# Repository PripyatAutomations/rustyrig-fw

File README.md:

# RustyRig

**Share radios, audio, and station resources over a network.**

RustyRig is a GPLv2-licensed, open-source, multi-user amateur-radio platform. Operate radios from another computer, listen with friends, or bring multiple stations together. Operators get live radio controls, audio, chat, and access to the resources they are allowed to use.

RustyRig is under active development. The current releases are for testing; features and configuration can change.

WebUI will be returning in v2.0! The v1.x series is focusing on improving
transport reliability by adding RTP (done!), mesh server links (almost done), 
and multihome client connections (pending).

Currently this is NOT usable out of the box on non-linux hosts, we'll revisit that soon with libmongoose!

## What you can do

- **Operate together.** Join radio rooms, see who's online, chat, and coordinate transmitter access.
- **Control more than one radio.** Work with supported Hamlib radios and networked rig-control backends.
- **Listen and transmit remotely.** Route receive and transmit audio over the network, with codec selection and per-stream controls.
- **Choose your interface.** Use the Linux GTK desktop client, terminal client, or browser interface.
- **Connect stations.** Link servers to access authorized remote rooms and station resources.
- **Explore SDR receivers.** Browse and connect to supported remote receivers through the SDR Directory.

Additional tools include remote serial/GPS access, audio recording, administration, and station resource discovery.

## See it in action

| Desktop client | Terminal client |
| --- | --- |
|  |  |

| Settings | Browser client |
| --- | --- |
|  |  |

| SDR Browser | SDR Receiver |
| --- | --- |
|  |  |

### Resource Explorer

### Audio Routing

## Get started

RustyRig currently targets Debian-family Linux distributions for building and packaging.

The recommended multi-project build is [rrpk](https://github.com/PripyatAutomations/rrpk),
which clones, builds and installs `librustyaxe`, `librrprotocol`,
`callsign-lookup`, and finally `rustyrig-fw` as independent repositories
in dependency order. **These three projects are not bundled or submodules of
rustyrig-fw.** For a standalone RustyRig build, install their respective
development packages first.

```sh
git clone https://github.com/PripyatAutomations/rustyrig-fw.git
# Install librustyaxe-dev, librrprotocol-dev and librustyirc-dev separately before building.
cd rustyrig-fw
./install-deps.sh
```

The native OpenSSL/wslay build does not fetch Mongoose or generate an EEPROM image.
Run `make PROFILE=radio buildconf` to generate only the application
configuration header; the normal `make PROFILE=radio` does that automatically.
Embedded EEPROM builds can opt in with `make PROFILE=radio USE_EEPROM=true`.
Mongoose is disabled by default and only fetched with an explicit
`USE_MONGOOSE=true` build/update through `tools/update-optional-sources.sh`.

The dependency helper prints the installation command for your selected build profile. Follow the instructions it produces, then continue with the **[quickstart](QUICKSTART.txt)** to build, configure a station, and connect your first client.

**New to RustyRig?** Start with a single server and one radio—or Hamlib's dummy backend—before enabling additional stations or transmit functions.

## Documentation

| Guide | When to read it |
| --- | --- |
| [Quickstart](QUICKSTART.txt) | First installation, login, and connection |
| [Operator guide](doc/operator-guide.md) | Tuning, audio, rooms, SDRs and troubleshooting |
| [Installation and packaging](doc/INSTALLING) | Package and service installation |
| [Radio rooms](doc/rig-rooms.md) | Multiple rigs, room access, and VFO/audio behavior |
| [Audio codecs](doc/media-codecs.md) | Selecting codecs and setting up audio pipelines |
| [IRC client settings](doc/irc-client.md) | Multiple connections and proxies |
| [Serial devices, server exports and privileges](doc/serial-interfaces.md) | Map physical UART/USB devices, grant per-device access, attach from clients, and understand mesh limitations |
| [Known issues](doc/KNOWN-ISSUES.md) | Open RC problems and requested fixes |
| [Changelog](CHANGELOG) | Recent changes and known transitions |
| [RC release checklist](doc/release-checklist.md) | Build, package, smoke-test and tag a release |
| [Release packaging guide](doc/RELEASING.md) | Debian RC versions, reproducible builds and upgrades |
| [Debian archive readiness](doc/debian-archive-readiness.md) | Sponsor-facing blockers, license inventory and clean-build checks |
| [Debian source/package split](doc/debian-source-split.md) | External library source packages and retained rrserver/rrclient/rrbridge binary split |
| [Server maintenance](doc/server-maintenance.md) | Confirmed database, log, recording and identity resets |
| [Remote SDR architecture](doc/remote-sdr-architecture.md) | Design proposal, **not implemented functionality** |

Configuration examples live in [`config/`](config/). Use `/help` in the client for commands.

## NOTES

This is an early version, especially backend.yaesu -- please don't use it
unattended until you test it thoroughly in your setup.

CAT emulator currently has very limited 991a support and you probably should
select ft891 in your program for now if trying to use it.

Yaesu backend has experimental support for ft991(a) support. If it doesnt
work well, let me know and in the meanwhile try hamlib backend.

## For developers

The main pieces are `rrserver` (server), `rrclient` (GTK/TUI), `rrbridge` (SDR bridges), `librrprotocol` (shared protocol), `librustyaxe` (application support), and `fwdsp` / `libfwdspmgr` (audio). The browser UI is developed in [rustyrig-www](https://github.com/PripyatAutomations/rustyrig-www).

Contributions, hardware compatibility reports, documentation improvements, and reproducible bug reports are welcome. See the [issue tracker](https://github.com/PripyatAutomations/rustyrig-fw/issues).

## License

RustyRig-owned code is licensed under the **GNU General Public License,
version 2 only** (`GPL-2.0-only`); see [doc/LICENSE](doc/LICENSE).
The independently installed `librrprotocol` library is GPLv2. The `librustyaxe` library retains
its MIT license. Other bundled components, dependencies and Windows themes
retain their respective upstream licenses.

For a complete mesh bootstrap or post-compromise credential rotation, see the
[cluster rebuild and breach-recovery runbook](doc/cluster-rebuild-recovery.md).

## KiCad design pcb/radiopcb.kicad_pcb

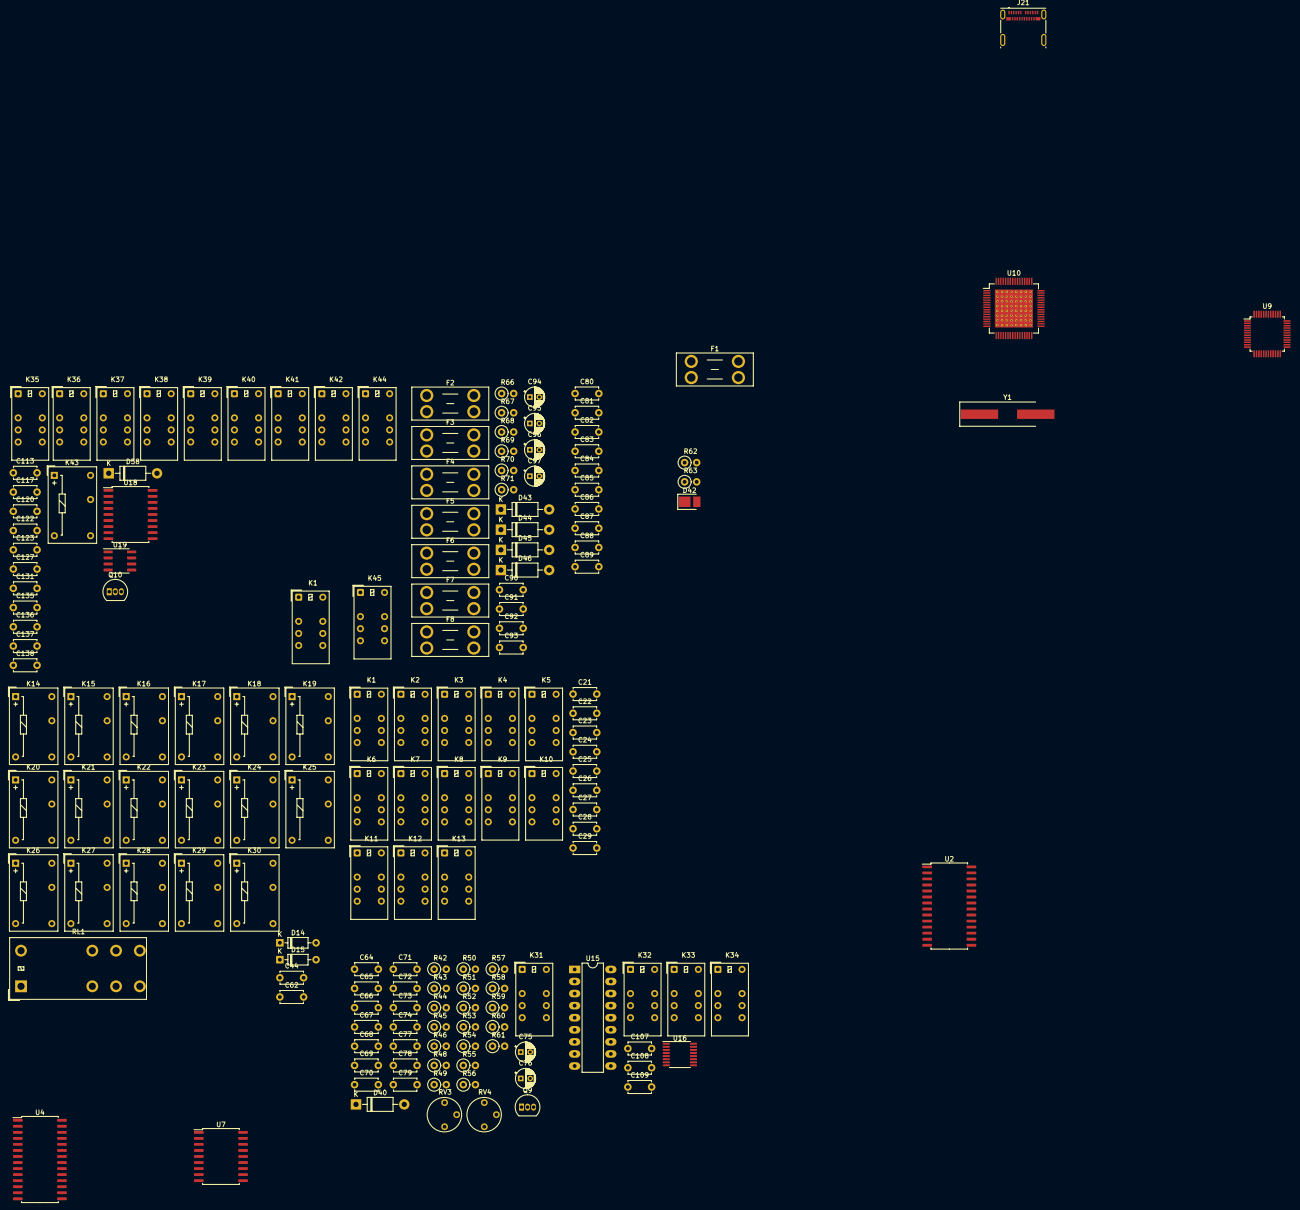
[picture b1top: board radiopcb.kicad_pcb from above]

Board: 2 copper layers, 165 parts (0 on the bottom side), 130 nets, no tracks yet.

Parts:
C21, C22, C23, C24, C25, C26, C27, C28, C29, C44, C62, C64, C65, C66, C67, C68, C69, C70, C71, C72, C73, C74, C77, C78, C79, C80, C81, C86, C87, C88, C89, C107, C108, C109, C113, C117, C120, C122, C123, C127, C131, C135, C136, C137, C138: 0.1u; C_Disc_D4.7mm_W2.5mm_P5.00mm
C75, C76: 470u; CP_Radial_D4.0mm_P2.00mm
C82, C83, C90: 10u; C_Disc_D4.7mm_W2.5mm_P5.00mm
C84, C85: 18p; C_Disc_D4.7mm_W2.5mm_P5.00mm
C91, C92: 100n; C_Disc_D4.7mm_W2.5mm_P5.00mm
C93: 47u; C_Disc_D4.7mm_W2.5mm_P5.00mm
C94, C95: 220u; CP_Radial_D4.0mm_P2.00mm
C96, C97: 10u; CP_Radial_D4.0mm_P2.00mm
D14, D15: 1N4148; D_DO-35_SOD27_P7.62mm_Horizontal
D40, D43, D44, D45, D46, D58: 1N4001; D_DO-41_SOD81_P10.16mm_Horizontal
D42: LED-Green; LED_PLCC_2835_Handsoldering
F1, F6: 3A; Fuseholder_Blade_Mini_Keystone_3568
F2, F3: 30A; Fuseholder_Blade_Mini_Keystone_3568
F4, F5: 5A; Fuseholder_Blade_Mini_Keystone_3568
F7, F8: 250mA; Fuseholder_Blade_Mini_Keystone_3568
J21: USB; USB_C_Receptacle_Molex_105450-0101
K1, K1#2, K2, K3, K4, K5, K6, K7, K8, K9, K10, K11, K12, K13, K31, K32, K33, K34, K35, K36, K37, K38, K39, K40, K41, K42, K44, K45: EC2-5SNU; Relay_DPDT_Kemet_EC2
K14, K15, K16, K17, K18, K19, K20, K21, K22, K23, K24, K25, K26, K27, K28, K29, K30, K43: G6E; Relay_SPDT_Omron_G6E
Q9: 2N3904; TO-92_Inline
Q10: BT169B; TO-92_Inline
R42, R43, R52, R53: 1K; R_Axial_DIN0207_L6.3mm_D2.5mm_P2.54mm_Vertical
R44, R45, R48, R49, R50, R51, R54, R55: 22; R_Axial_DIN0207_L6.3mm_D2.5mm_P2.54mm_Vertical
R46, R56: 2.2K; R_Axial_DIN0207_L6.3mm_D2.5mm_P2.54mm_Vertical
R57, R58: 47; R_Axial_DIN0207_L6.3mm_D2.5mm_P2.54mm_Vertical
R59, R60: 220; R_Axial_DIN0207_L6.3mm_D2.5mm_P2.54mm_Vertical
R61: 1k; R_Axial_DIN0207_L6.3mm_D2.5mm_P2.54mm_Vertical
R62, R68, R69, R70, R71: 10M; R_Axial_DIN0207_L6.3mm_D2.5mm_P2.54mm_Vertical
R63: 9.53K; R_Axial_DIN0207_L6.3mm_D2.5mm_P2.54mm_Vertical
R66: 10k; R_Axial_DIN0207_L6.3mm_D2.5mm_P2.54mm_Vertical
R67: 54.9k; R_Axial_DIN0207_L6.3mm_D2.5mm_P2.54mm_Vertical
RL1: Bypass; Relay_DPDT_Panasonic_JW2
RV3, RV4: 10K; Potentiometer_Vishay_T7-YA_Single_Vertical
U2, U4: MCP23017_SO; SOIC-28W_7.5x17.9mm_P1.27mm
U7, U18: MCP23008-xSO; SOIC-18W_7.5x11.6mm_P1.27mm
U9: CM119B; TQFP-48_7x7mm_P0.5mm
U10: TUSB4041I; HTQFP-64-1EP_10x10mm_P0.5mm_EP8x8mm_Mask4.4x4.4mm_ThermalVi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
U15: ULN2804A; DIP-18_W7.62mm_LongPads
U16: 74HC596; TSSOP-16_4.4x5mm_P0.65mm
U19: LM555xM; SOIC-8_3.9x4.9mm_P1.27mm
Y1: 24Mhz; Crystal_SMD_HC49-SD_HandSoldering

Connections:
+1V1: C82.1, F8.1, U10.19 (VDD), U10.25 (VDD), U10.37 (VDD), U10.45 (VDD), U10.53 (VDD), U10.60 (VDD), U10.63 (VDD)
+3.3V: C83.1, F7.1, U9.7 (PWRSEL), U9.38 (MSEL), U10.2 (VDD33), U10.20 (VDD33), U10.31 (VDD33), U10.48 (VDD33)
+5V: C23.2, C24.2, C44.2, C62.2, C80.1, C81.1, C89.1, C122.2, F1.1, F6.2, K32.1, K33.1, K34.1, Q9.3 (C), U2.9 (VDD), U4.9 (VDD), U4.15 (A0), U7.4 (A1), U7.18 (VDD), U9.29 (AVDD), U9.34 (AVDD), U9.35 (DVDD), U18.18 (VDD)
+12V: C21.2, C76.1, C79.2, C120.2, F5.1, K1.1, K1#2.1, K2.1, K3.1, K4.1, K5.1, K6.1, K7.1, K8.1, K9.1, K10.1, K11.1, K12.1, K13.1, K14.1, K15.1, K16.1, K17.1, K18.1, K19.1, K20.1, K21.1, K22.1, K23.1, K24.1, K25.1, K26.1, K27.1, K28.1, K29.1, K30.1, K35.1, K36.1, K37.1, K38.1, K39.1, K40.1, K41.1, K42.1, K44.1, K45.1, RL1.1
+BATT: F3.1, F3.2, F4.1, F5.2
Earth: C21.1, C22.1, C23.1, C24.1, C25.2, C26.2, C27.2, C28.2, C29.2, C44.1, C62.1, C65.1, C68.1, C68.2, C69.1, C74.1, C75.2, C76.2, C77.1, C78.1, C79.1, C80.2, C81.2, C82.2, C83.2, C84.2, C85.2, C86.2, C87.2, C88.2, C89.2, C107.1, C108.1, C109.1, C113.1, C117.1, C120.1, C122.1, C123.1, C127.1, C131.1, C135.1, C136.1, C137.2, C138.2, D42.1 (K), J21.A1 (GND), J21.A5 (CC1), J21.A8 (SBU1), J21.A12 (GND), J21.B1 (GND), J21.B5 (CC2), J21.B8 (SBU2), J21.B12 (GND), J21.S1 (SHIELD), K31.8, R48.1, R49.2, R50.1, R51.2, R54.1, R55.2, R56.1, R63.1, RV3.3, RV4.3, U2.10 (VSS), U2.15 (A0), U2.16 (A1), U2.17 (A2), U4.10 (VSS), U4.16 (A1), U4.17 (A2), U7.3 (A2), U7.5 (A0), U7.9 (VSS), U9.10 (MODE), U10.65 (VSS), U15.9 (GND), U16.8 (GND), U18.3 (A2), U18.4 (A1), U18.5 (A0), U18.9 (VSS), Y1.2
GND: C90.1, C91.1, C93.2, C94.2, C95.2, C96.2, C97.2, D58.2 (A), F2.2, K43.6, R66.1, R69.2, R71.2, U19.1 (GND)
GNDA: U9.24 (AVSS), U9.33 (AVSS)
GNDD: U9.14 (DVSS), U9.36 (DVSS)
unnamed: K1.5, K1#2.5
unnamed: K1.8, K1#2.8
unnamed: C64.2, R42.1, R43.2, R44.2
unnamed: C66.2, R48.2, R53.1
unnamed: C67.2, R49.1, R52.1
unnamed: C69.2, R57.2, RV3.2
unnamed: C70.2, C73.1, R57.1
unnamed: C71.2, C72.2, R58.1
unnamed: C72.1, R59.1
unnamed: C73.2, R60.1
unnamed: C74.2, R58.2, RV4.2
unnamed: C75.1, C78.2
unnamed: C93.1, C94.1, C95.1, R67.2
unnamed: K1.12, K1#2.12
unnamed: C22.2, K8.12
unnamed: C25.1, K9.12
unnamed: C26.1, K10.12
unnamed: C27.1, K11.12
unnamed: C28.1, K12.12
unnamed: C29.1, K13.12
unnamed: D40.2 (A), K31.12
unnamed: D40.1 (K), K31.1
unnamed: D42.2 (A), U9.12 (LEDO)
unnamed: C97.1, D43.2 (A), D44.1 (K), D45.1 (K), F7.2, R68.1
unnamed: C96.1, D43.1 (K), F6.1
unnamed: D44.2 (A), R68.2, R69.1
unnamed: D45.2 (A), D46.1 (K), F8.2, R70.1
unnamed: D46.2 (A), R70.2, R71.1
unnamed: K32.12, U15.11 (O8)
unnamed: K33.12, U15.12 (O7)
unnamed: K34.12, U15.13 (O6)
unnamed: C113.2, K35.12
unnamed: C117.2, K36.12
unnamed: C123.2, K37.12
unnamed: C127.2, K38.12
unnamed: C131.2, K39.12
unnamed: C135.2, K40.12
unnamed: C136.2, K41.12
unnamed: C137.1, K42.12
unnamed: D58.1 (K), K43.1
unnamed: C138.1, K44.12
unnamed: K1#2.4, K45.8
unnamed: U4.13 (SDA), U7.2 (SDA)
unnamed: U4.12 (SCK), U7.1 (SCL)
unnamed: K31.5, K31.10
unnamed: U16.11 (SRCLK), U16.12 (RCLK)
unnamed: C107.2, C108.2, C109.2, U15.10 (COM), U16.16 (VCC)
unnamed: K1.4, K13.4
unnamed: K1.3, K1.10, K1#2.3, K1#2.10
unnamed: K2.4, K45.9
unnamed: K2.9, K3.4
unnamed: K2.3, K2.10
unnamed: K3.9, K4.4
unnamed: K3.3, K3.10
unnamed: K4.9, K5.4
unnamed: K4.3, K4.10
unnamed: K5.9, K6.4
unnamed: K5.3, K5.10
unnamed: K6.9, K7.4
unnamed: K6.3, K6.10
unnamed: K7.9, K8.4
unnamed: K7.3, K7.10
unnamed: K8.3, K8.10
unnamed: K9.3, K9.10
unnamed: K10.4, K11.9
unnamed: K9.4, K10.9
unnamed: K10.3, K10.10
unnamed: K11.4, K12.9
unnamed: K11.3, K11.10
unnamed: K12.4, K13.9
unnamed: K12.3, K12.10
unnamed: K13.3, K13.10
unnamed: K14.7, K15.7, K16.7, K17.7, K18.7, K19.7, K20.7, K21.7, K22.7
unnamed: K22.10, K26.7, K29.7, RL1.5
unnamed: K22.12, K25.7, RL1.4
unnamed: K23.7, K24.10
unnamed: K23.10, K27.10, K30.7
unnamed: K24.7, K25.10
unnamed: K27.7, K28.10
unnamed: K28.7, K29.10
unnamed: K32.4, K33.9
unnamed: K32.3, K32.10
unnamed: K33.4, K34.9
unnamed: K33.3, K33.10
unnamed: K34.3, K34.10
unnamed: K35.4, K36.9
unnamed: K35.3, K35.10
unnamed: K36.4, K37.9
unnamed: K36.3, K36.10
unnamed: K37.4, K38.9
unnamed: K37.3, K37.10
unnamed: K38.4, K39.9
unnamed: K38.3, K38.10
unnamed: K39.4, K40.9
unnamed: K39.3, K39.10
unnamed: K40.4, K41.9
unnamed: K40.3, K40.10
unnamed: K41.3, K41.10
unnamed: K42.3, K42.10
unnamed: K44.3, K44.10
unnamed: K45.3, K45.10
unnamed: Q9.2 (B), R61.2
unnamed: C77.2, Q9.1 (E), RV3.1, RV4.1
unnamed: R42.2, R44.1, R45.1
unnamed: RL1.2, RL1.7
unnamed: C65.2, R46.1
unnamed: U9.42 (USBDM), U10.57 (USB_DM_DN4)
unnamed: U9.41 (USBDP), U10.56 (USB_DP_DN4)
unnamed: R63.2, U10.32 (USB_R1)
unnamed: C84.1, R62.2, U10.30 (XI)
unnamed: C85.1, R62.1, U10.29 (XO), Y1.1
unnamed: C90.2, C91.2, F4.2
unnamed: R66.2, R67.1
unnamed: U15.1 (I1), U16.15 (QA)
unnamed: U15.2 (I2), U16.1 (QB)
unnamed: U15.3 (I3), U16.2 (QC)
unnamed: U15.4 (I4), U16.3 (QD)
unnamed: U15.5 (I5), U16.4 (QE)
unnamed: U15.6 (I6), U16.5 (QF)
unnamed: U15.7 (I7), U16.6 (QG)
unnamed: U15.8 (I8), U16.7 (QH)
